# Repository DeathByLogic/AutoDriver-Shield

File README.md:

AutoDriver SPI over RS-485 Shield
=================

Shield for the Sparkfun AutoDriver stepper motor driver to communicate with SPI over RS-485. This allows for communications to and from the AutoDriver over long distances. The companion to this board is the Arduino SPI over RS-485 Shield.

https://www.sparkfun.com/products/11611

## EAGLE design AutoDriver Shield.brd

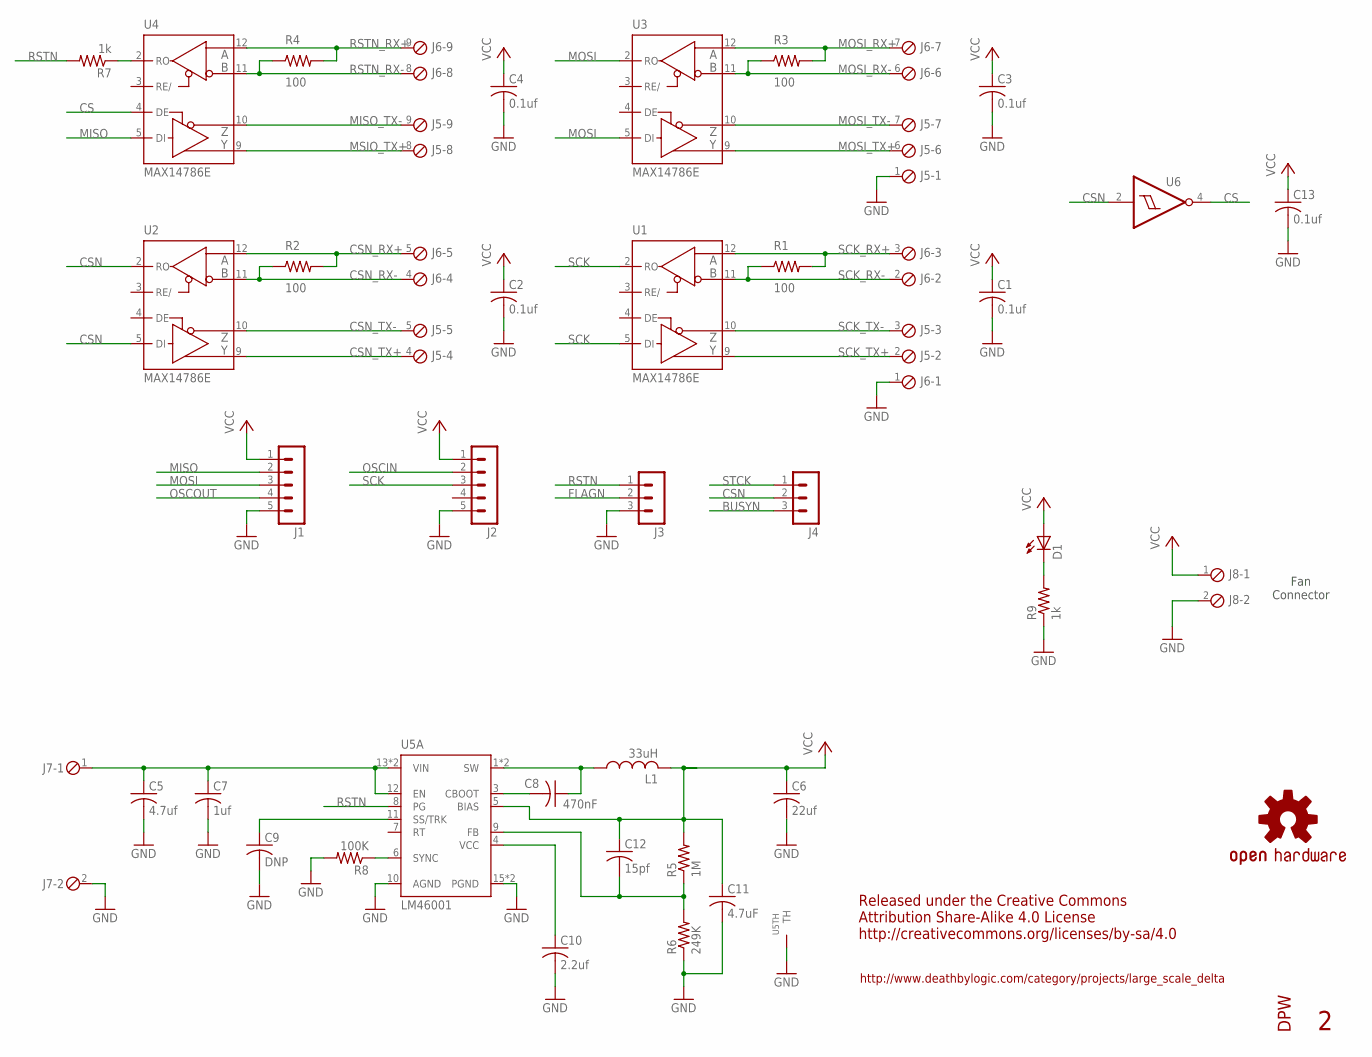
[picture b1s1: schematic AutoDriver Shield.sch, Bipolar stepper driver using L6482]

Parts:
C1, C2, C3, C4, C13: 0.1uf; C0805K
C5: 4.7uf; C1210K
C6: 22uf; C1210K
C7: 1uf; C1206K
C8: 470nF; C0805K
C9: DNP; C0603K
C10: 2.2uf; C0603K
C11: 4.7uF; C0805K
C12: 15pf; C0805K
D1: LEDCHIPLED_0805; CHIPLED_0805
J1, J2: MA05-1
J3, J4: MA03-1
J5, J6: MPT9; 9POL254
J7, J8: MPT2; 2POL254
L1: 33uH; L6045
LOGO1: OSHW-LOGOM; OSHW-LOGO-M
R1, R2, R3, R4: 100; R1206
R5: 1M; R0402
R6: 249K; R0402
R7, R9: 1k; R0805
R8: 100K; R0402
U1, U2, U3, U4: MAX14786E; SO14
U5: LM46001; HTSSOP16PWP
U6: 74AHC1G14; SOT23-5
U$2: PENGUIN_LOGOSILKSCREEN; PENGUIN_SILKSCREEN

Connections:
BUSYN: J4.3
CS: U4.4 (DE), U6.4 (O)
CSN: J4.2, U2.2 (RO), U2.5 (DI), U6.2 (I)
CSN_RX+: J6.5, R2.2, U2.12 (A)
CSN_RX-: J6.4, R2.1, U2.11 (B)
CSN_TX+: J5.4, U2.9 (Y)
CSN_TX-: J5.5, U2.10 (Z)
FLAGN: J3.2
GND: C1.2, C2.2, C3.2, C4.2, C5.2, C6.2, C7.2, C9.2, C10.2, C11.2, C13.2, J1.5, J2.5, J3.3, J5.1, J6.1, J7.2, J8.2, R6.1, R8.2, R9.1, U1.6 (GND), U1.7 (GND), U2.6 (GND), U2.7 (GND), U3.6 (GND), U3.7 (GND), U4.6 (GND), U4.7 (GND), U5.10 (AGND), U5.15 (PGND), U5.16 (PGND), U5.TH1 (TH), U5.TH2 (TH), U5.TH3 (TH), U5.TH4 (TH), U5.TH5 (TH), U5.TH6 (TH), U5.TH7 (TH), U5.TH8 (TH), U5.TH9 (TH), U5.TH10 (TH), U5.TH11 (TH), U5.TH12 (TH), U5.THA (TH), U5.THB (TH), U6.3 (GND)
MISO: J1.2, U4.5 (DI)
MISO_TX-: J5.9, U4.10 (Z)
MOSI: J1.3, U3.2 (RO), U3.5 (DI)
MOSI_RX+: J6.7, R3.2, U3.12 (A)
MOSI_RX-: J6.6, R3.1, U3.11 (B)
MOSI_TX+: J5.6, U3.9 (Y)
MOSI_TX-: J5.7, U3.10 (Z)
MSIO_TX+: J5.8, U4.9 (Y)
unnamed: D1.C, R9.2
unnamed: C5.1, C7.1, J7.1, U5.12 (EN), U5.13 (VIN), U5.14 (VIN)
unnamed: C9.1, U5.11 (SS/TRK)
unnamed: R8.1, U5.6 (SYNC)
unnamed: C8.1, L1.P$1 (1), U5.1 (SW), U5.2 (SW)
unnamed: C8.2, U5.3 (CBOOT)
unnamed: R7.1, U4.2 (RO)
unnamed: C10.1, U5.4 (VCC)
unnamed: C12.2, R5.1, R6.2, U5.9 (FB)
OSCIN: J2.2
OSCOUT: J1.4
RSTN: J3.1, R7.2, U5.8 (PG)
RSTN_RX+: J6.9, R4.2, U4.12 (A)
RSTN_RX-: J6.8, R4.1, U4.11 (B)
SCK: J2.3, U1.2 (RO), U1.5 (DI)
SCK_RX+: J6.3, R1.2, U1.12 (A)
SCK_RX-: J6.2, R1.1, U1.11 (B)
SCK_TX+: J5.2, U1.9 (Y)
SCK_TX-: J5.3, U1.10 (Z)
STCK: J4.1
VCC: C1.1, C2.1, C3.1, C4.1, C6.1, C11.1, C12.1, C13.1, D1.A, J1.1, J2.1, J8.1, L1.P$2 (2), R5.2, U1.14 (VCC), U2.14 (VCC), U3.14 (VCC), U4.14 (VCC), U5.5 (BIAS), U6.5 (VCC)

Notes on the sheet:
Released under the Creative Commons Attribution Share-Alike 4.0 License http://creativecommons.org/licenses/by-sa/4.0
http://www.deathbylogic.com/category/projects/large_scale_delta
Fan Connector

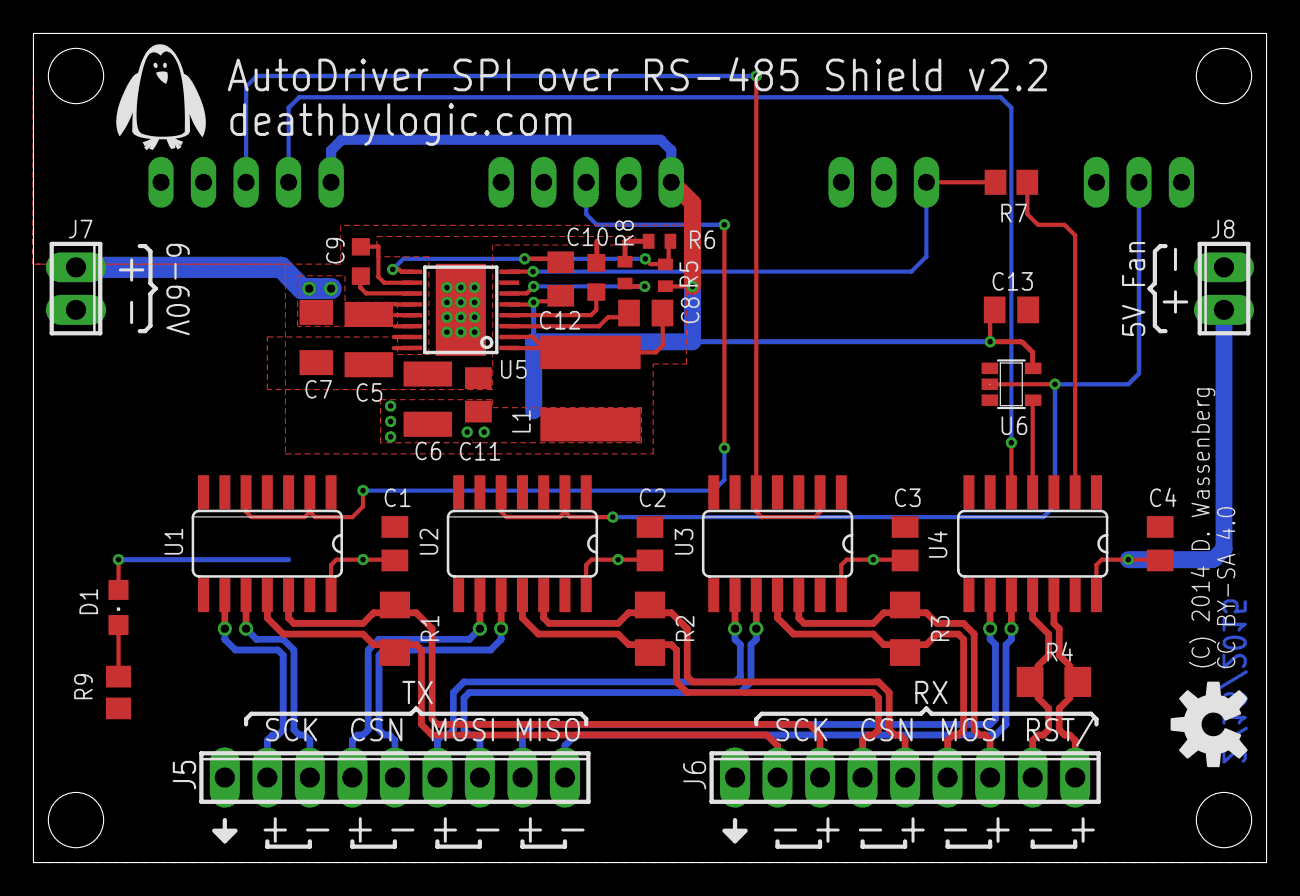
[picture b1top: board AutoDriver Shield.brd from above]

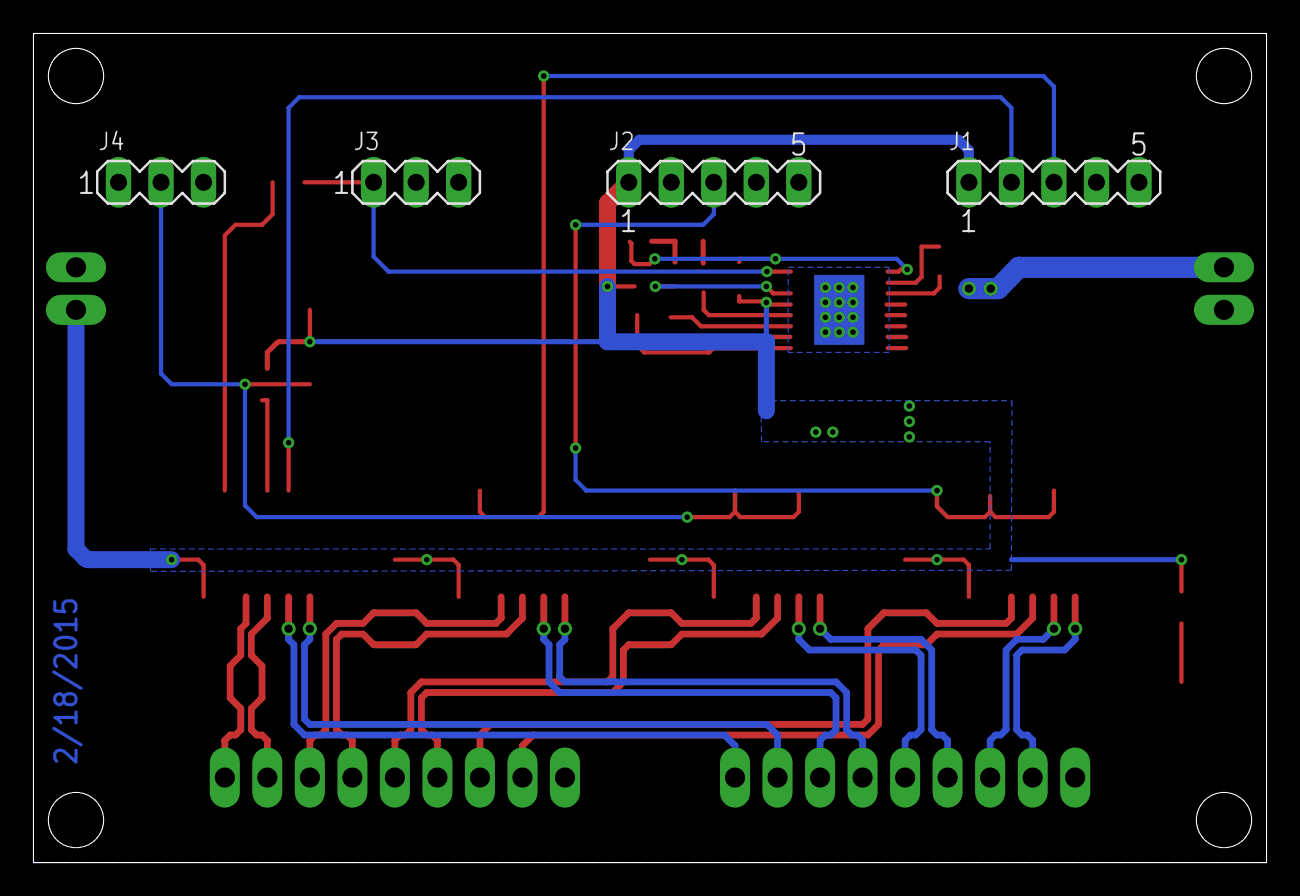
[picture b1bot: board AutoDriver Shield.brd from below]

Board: 2 copper layers, 73.7 x 49.5 mm, 44 parts (4 on the bottom side), 33 nets.

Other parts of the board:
STANDOFF1, STANDOFF2, STANDOFF3, STANDOFF4: STAND-OFF

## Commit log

2014-09-14 Removed unneeded files
2014-09-14 Spelling correction
2014-10-14 Added missing trace connecting U1 pin 2 to SCK signals.
2014-11-16 Updated gerber files to include missing trace added to board layout.
2015-02-19 Removed Non-Commercial License; Updated website address.

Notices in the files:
AutoDriver Shield.brd:
(C) 2014 D. Wassenberg
CC BY-SA 4.0
parts and their libraries:
SparkFun-Aesthetics: Licensing: CC v3.0 Share-Alike You are welcome to use this library for commercial purposes.
